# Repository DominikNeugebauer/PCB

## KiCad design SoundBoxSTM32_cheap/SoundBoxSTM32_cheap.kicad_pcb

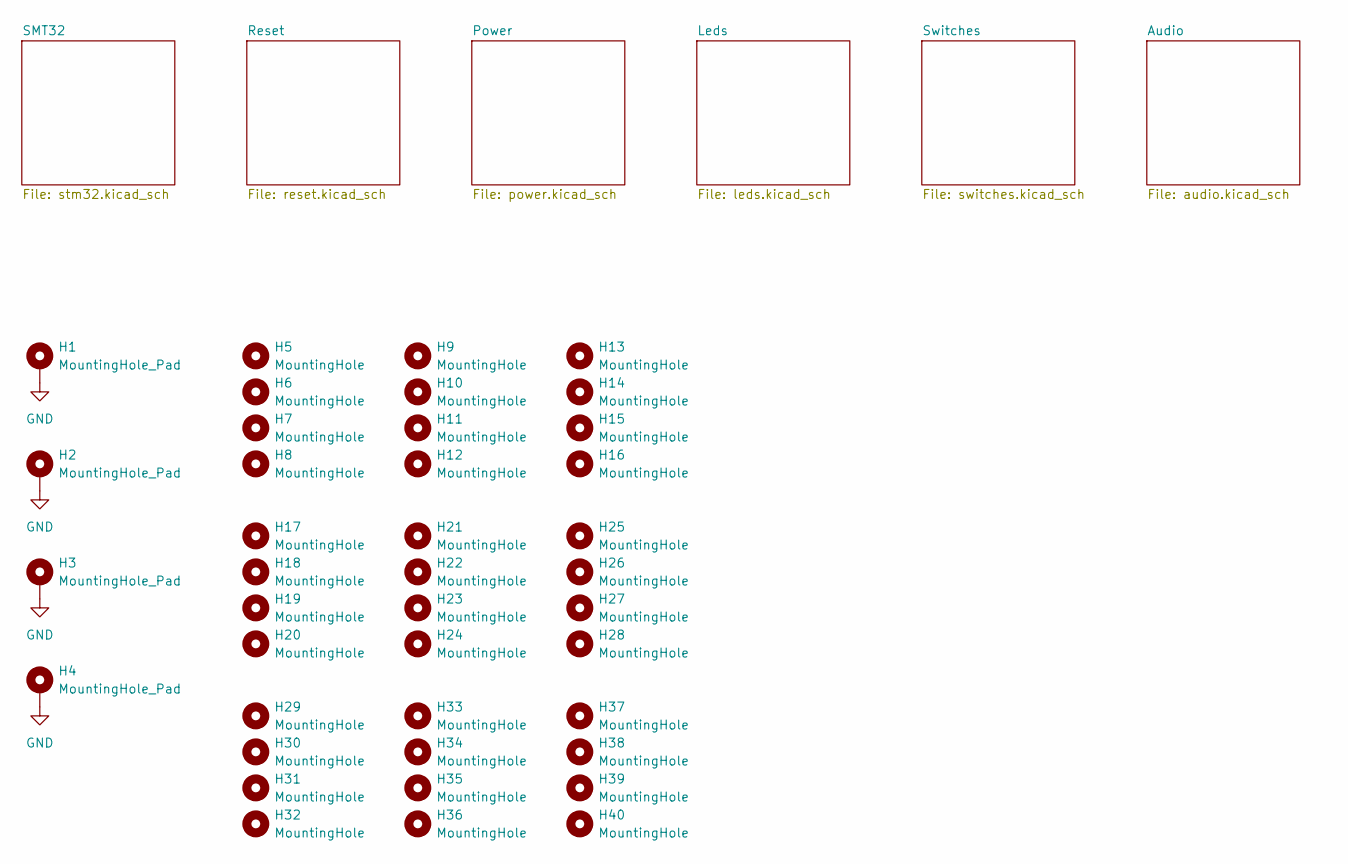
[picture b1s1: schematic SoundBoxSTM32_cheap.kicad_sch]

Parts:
H1, H2, H3, H4: MountingHole_Pad; MountingHole_5.3mm_M5_DIN965_Pad
H5, H6, H7, H8, H9, H10, H11, H12, H13, H14, H15, H16, H17, H18, H19, H20, H21, H22, H23, H24, H25, H26, H27, H28, H29, H30, H31, H32, H33, H34, H35, H36, H37, H38, H39, H40: MountingHole; MountingHole_5.3mm_M5

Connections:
GND: H1.1 (1_1), H2.1 (1_1), H3.1 (1_1), H4.1 (1_1); also elsewhere on the board

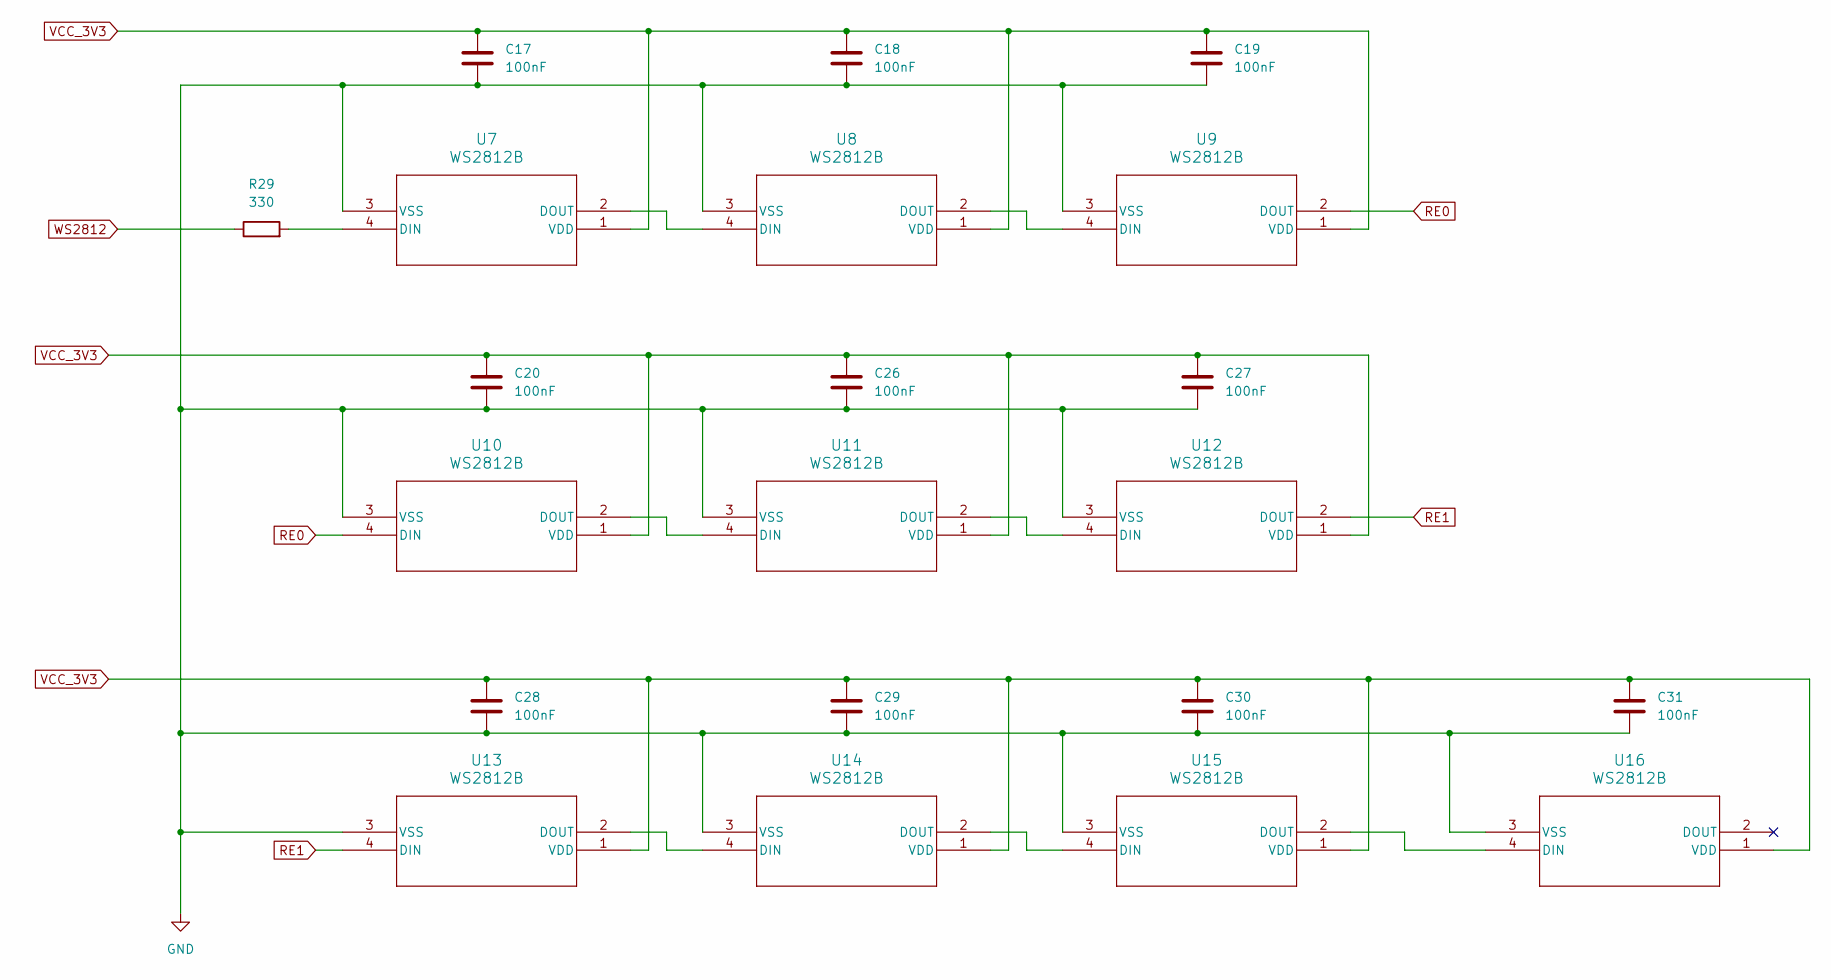
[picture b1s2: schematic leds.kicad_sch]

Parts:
C17, C18, C19, C20, C26, C27, C28, C29, C30, C31: 100nF; C_0603_1608Metric
R29: 330; R_0603_1608Metric
U7, U8, U9, U10, U11, U12, U13, U14, U15, U16: WS2812B; WS2812B_WDS

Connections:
GND: C17.2, C18.2, C19.2, C20.2, C26.2, C27.2, C28.2, C29.2, C30.2, C31.2, U7.3 (VSS), U8.3 (VSS), U9.3 (VSS), U10.3 (VSS), U11.3 (VSS), U12.3 (VSS), U13.3 (VSS), U14.3 (VSS), U15.3 (VSS), U16.3 (VSS); also elsewhere on the board
unnamed: R29.2, U7.4 (DIN)
unnamed: U7.2 (DOUT), U8.4 (DIN)
unnamed: U8.2 (DOUT), U9.4 (DIN)
unnamed: U10.2 (DOUT), U11.4 (DIN)
unnamed: U11.2 (DOUT), U12.4 (DIN)
unnamed: U13.2 (DOUT), U14.4 (DIN)
unnamed: U14.2 (DOUT), U15.4 (DIN)
unnamed: U15.2 (DOUT), U16.4 (DIN)
RE0: U9.2 (DOUT), U10.4 (DIN)
RE1: U12.2 (DOUT), U13.4 (DIN)
VCC_3V3: C17.1, C18.1, C19.1, C20.1, C26.1, C27.1, C28.1, C29.1, C30.1, C31.1, U7.1 (VDD), U8.1 (VDD), U9.1 (VDD), U10.1 (VDD), U11.1 (VDD), U12.1 (VDD), U13.1 (VDD), U14.1 (VDD), U15.1 (VDD), U16.1 (VDD); also elsewhere on the board
WS2812: R29.1; also elsewhere on the board

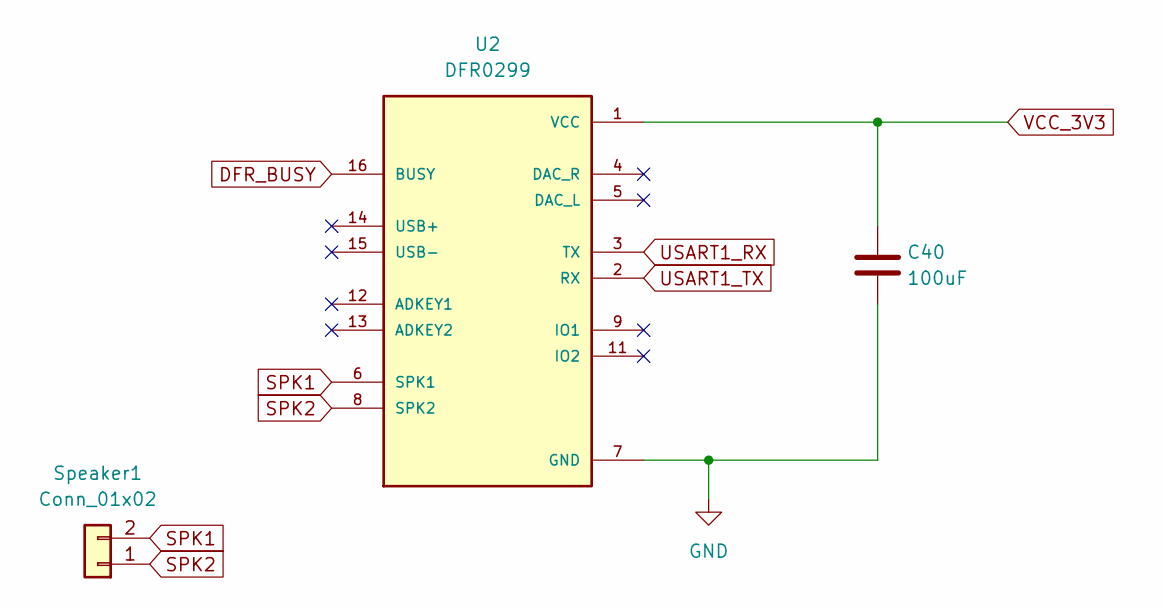
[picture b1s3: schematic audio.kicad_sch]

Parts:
C40: 100uF; C_1206_3216Metric_Pad1.33x1.80mm_HandSolder
Speaker1: Conn_01x02; PinHeader_1x02_P2.54mm_Vertical
U2: DFR0299

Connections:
DFR_BUSY: U2.16 (BUSY); also elsewhere on the board
GND: C40.2, U2.7 (GND), U2.10 (GND); also elsewhere on the board
SPK1: Speaker1.2, U2.6 (SPK1)
SPK2: Speaker1.1, U2.8 (SPK2)
USART1_RX: U2.3 (TX); also elsewhere on the board
USART1_TX: U2.2 (RX); also elsewhere on the board
VCC_3V3: C40.1, U2.1 (VCC); also elsewhere on the board

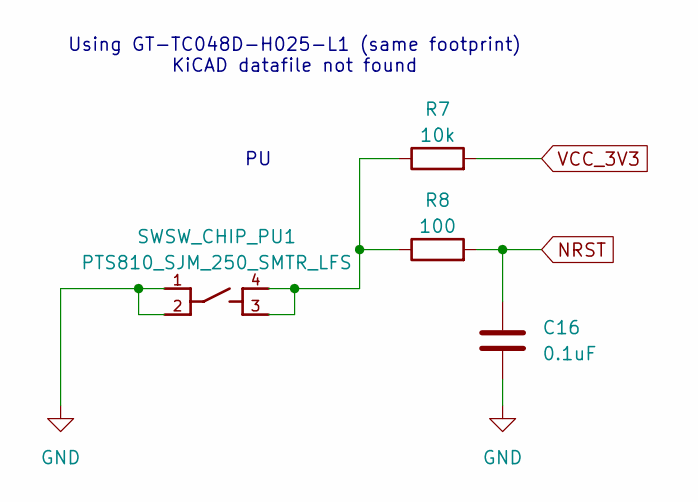
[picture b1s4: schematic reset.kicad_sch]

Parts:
C16: 0.1uF; C_0603_1608Metric
R7: 10k; R_0603_1608Metric
R8: 100; R_0603_1608Metric
SWSW_CHIP_PU1: PTS810_SJM_250_SMTR_LFS

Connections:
GND: C16.2, SWSW_CHIP_PU1.1, SWSW_CHIP_PU1.2; also elsewhere on the board
NRST: C16.1, R8.2; also elsewhere on the board
unnamed: R7.1, R8.1, SWSW_CHIP_PU1.3, SWSW_CHIP_PU1.4
VCC_3V3: R7.2; also elsewhere on the board

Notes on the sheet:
Using GT-TC048D-H025-L1 (same footprint) KiCAD datafile not found

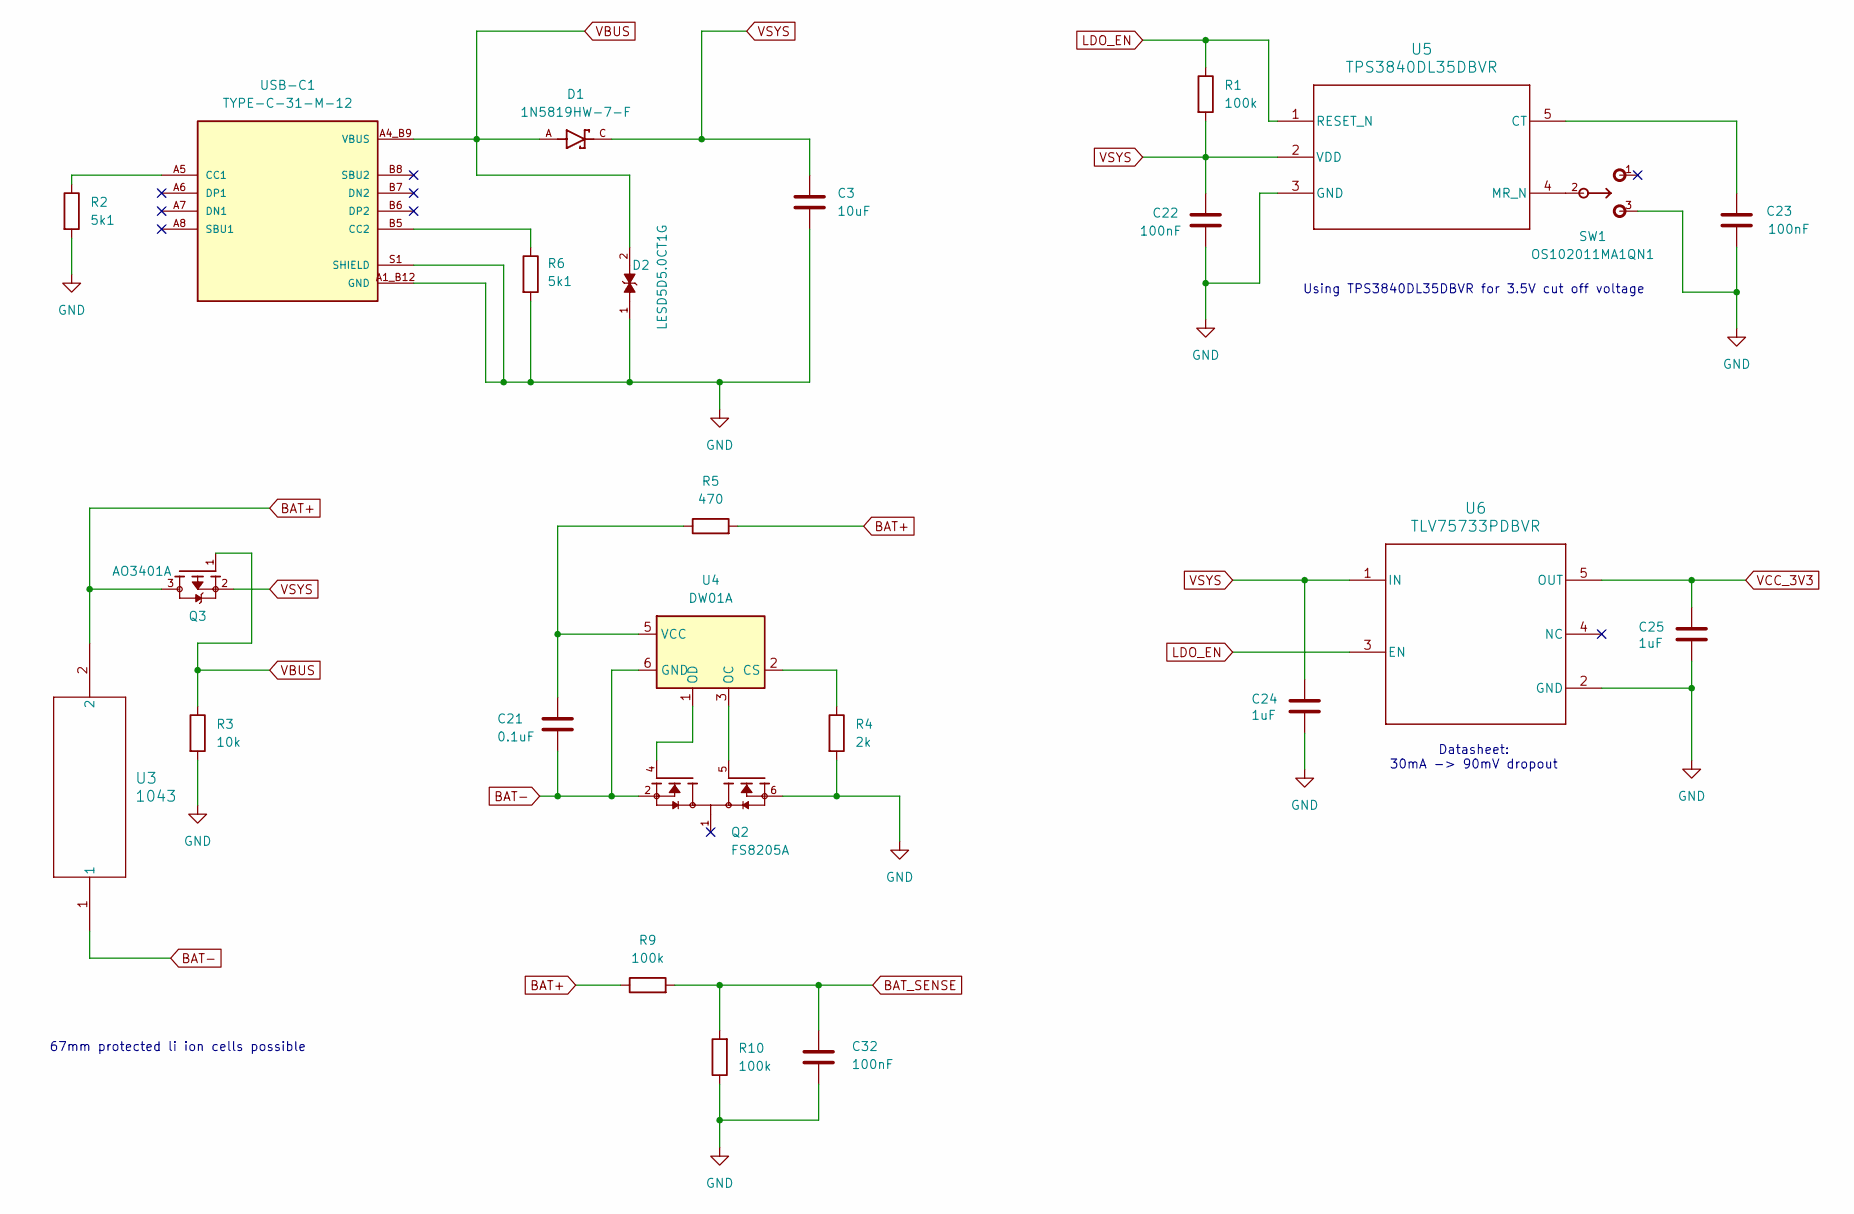
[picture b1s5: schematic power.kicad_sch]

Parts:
C3: 10uF; C_0603_1608Metric
C21: 0.1uF; C_0603_1608Metric
C22, C23, C32: 100nF; C_0603_1608Metric
C24, C25: 1uF; C_0603_1608Metric
D1: 1N5819HW-7-F; PARTREV 18-2
D2: LESD5D5.0CT1G; PARTREV O
Q2: FS8205A; PARTREV 1.7
Q3: AO3401A; PMOS-SOT23-3
R1, R9, R10: 100k; R_0603_1608Metric
R2, R6: 5k1; R_0603_1608Metric
R3: 10k; R_0603_1608Metric
R4: 2k; R_0603_1608Metric
R5: 470; R_0603_1608Metric
SW1: OS102011MA1QN1; MANUFACTURER_PART_NUMBER OS102011MA1QN1
U3: 1043; 1043_KEY
U4: DW01A; SOT-23-6
U5: TPS3840DL35DBVR; SOT-23-5
U6: TLV75733PDBVR; SOT95P280X145-5N_TLV75733PDBVR
USB-C1: TYPE-C-31-M-12; USB_TYPE-C-31-M-12; PARTREV 2020.12.08

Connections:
BAT+: Q3.3, R5.2, R9.1, U3.2
BAT-: C21.2, Q2.2, Q2.3, U3.1, U4.6 (GND)
BAT_SENSE: C32.1, R9.2, R10.2; also elsewhere on the board
GND: C3.2, C22.2, C23.2, C24.2, C25.2, C32.2, D2.1, Q2.6, Q2.7, R2.2, R3.2, R4.2, R6.2, R10.1, SW1.3, U5.3 (GND), U6.2 (GND), USB-C1.A1_B12 (GND), USB-C1.B1_A12 (GND), USB-C1.S1 (SHIELD), USB-C1.S2 (SHIELD), USB-C1.S3 (SHIELD), USB-C1.S4 (SHIELD); also elsewhere on the board
LDO_EN: R1.1, U5.1 (RESET_N), U6.3 (EN)
unnamed: R4.1, U4.2 (CS)
unnamed: Q2.5, U4.3 (OC)
unnamed: Q2.4, U4.1 (OD)
unnamed: C21.1, R5.1, U4.5 (VCC)
unnamed: C23.1, U5.5 (CT)
unnamed: SW1.2, U5.4 (MR_N)
unnamed: R2.1, USB-C1.A5 (CC1)
unnamed: R6.1, USB-C1.B5 (CC2)
VBUS: D1.A, D2.2, Q3.1, R3.1, USB-C1.A4_B9 (VBUS), USB-C1.B4_A9 (VBUS)
VCC_3V3: C25.1, U6.5 (OUT); also elsewhere on the board
VSYS: C3.1, C22.1, C24.1, D1.C, Q3.2, R1.2, U5.2 (VDD), U6.1 (IN)

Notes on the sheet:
Using TPS3840DL35DBVR for 3.5V cut off voltage
67mm protected li ion cells possible
Datasheet: 30mA -> 90mV dropout

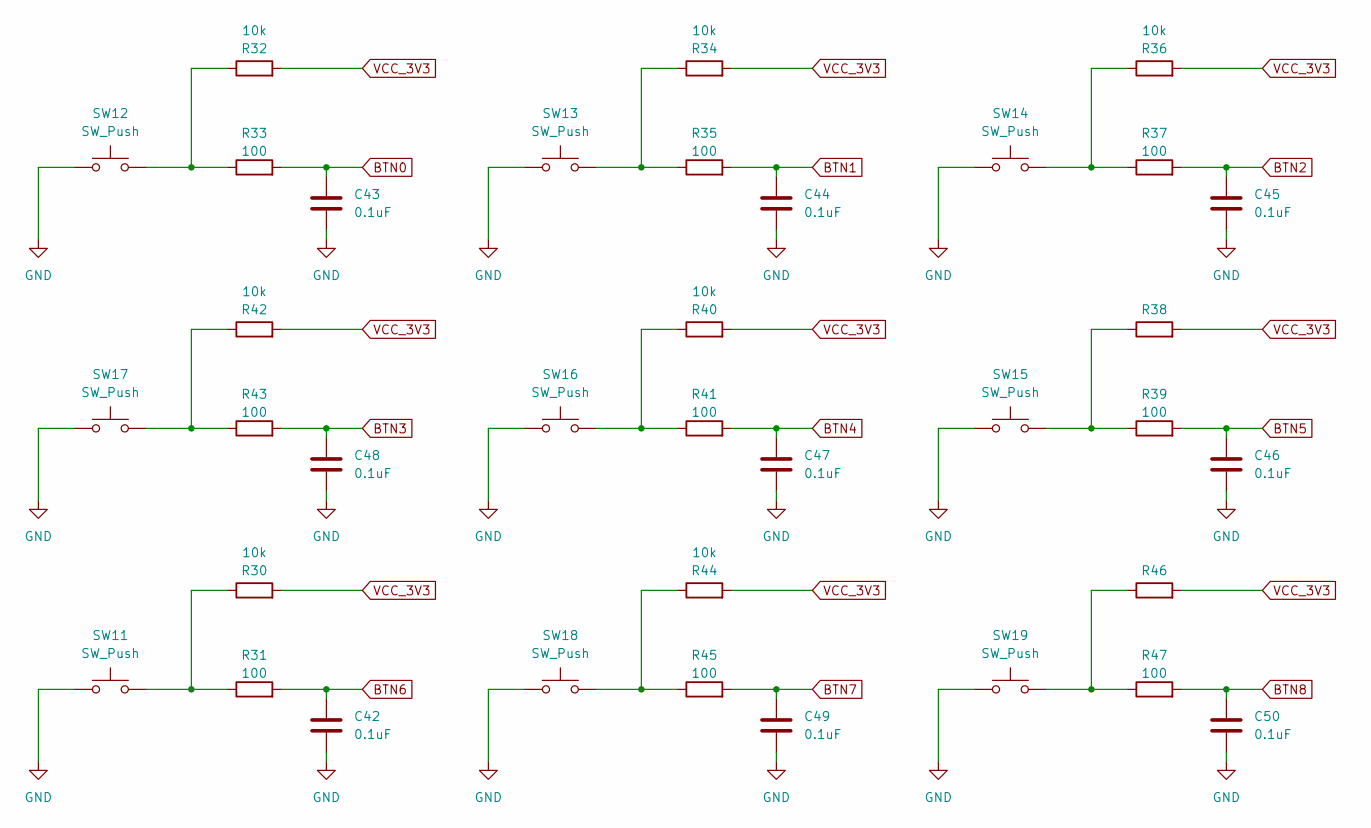
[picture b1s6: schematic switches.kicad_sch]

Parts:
C42, C43, C44, C45, C46, C47, C48, C49, C50: 0.1uF; C_0603_1608Metric
R30, R32, R34, R36, R38, R40, R42, R44, R46: 10k; R_0603_1608Metric
R31, R33, R35, R37, R39, R41, R43, R45, R47: 100; R_0603_1608Metric
SW11, SW12, SW13, SW14, SW15, SW16, SW17, SW18, SW19: SW_Push; SW_Cherry_MX_1.00u_PCB

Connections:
BTN0: C43.1, R33.2; also elsewhere on the board
BTN1: C44.1, R35.2; also elsewhere on the board
BTN2: C45.1, R37.2; also elsewhere on the board
BTN3: C48.1, R43.2; also elsewhere on the board
BTN4: C47.1, R41.2; also elsewhere on the board
BTN5: C46.1, R39.2; also elsewhere on the board
BTN6: C42.1, R31.2; also elsewhere on the board
BTN7: C49.1, R45.2; also elsewhere on the board
BTN8: C50.1, R47.2; also elsewhere on the board
GND: C42.2, C43.2, C44.2, C45.2, C46.2, C47.2, C48.2, C49.2, C50.2, SW11.1, SW12.1, SW13.1, SW14.1, SW15.1, SW16.1, SW17.1, SW18.1, SW19.1; also elsewhere on the board
unnamed: R30.1, R31.1, SW11.2
unnamed: R32.1, R33.1, SW12.2
unnamed: R34.1, R35.1, SW13.2
unnamed: R36.1, R37.1, SW14.2
unnamed: R38.1, R39.1, SW15.2
unnamed: R40.1, R41.1, SW16.2
unnamed: R42.1, R43.1, SW17.2
unnamed: R44.1, R45.1, SW18.2
unnamed: R46.1, R47.1, SW19.2
VCC_3V3: R30.2, R32.2, R34.2, R36.2, R38.2, R40.2, R42.2, R44.2, R46.2; also elsewhere on the board

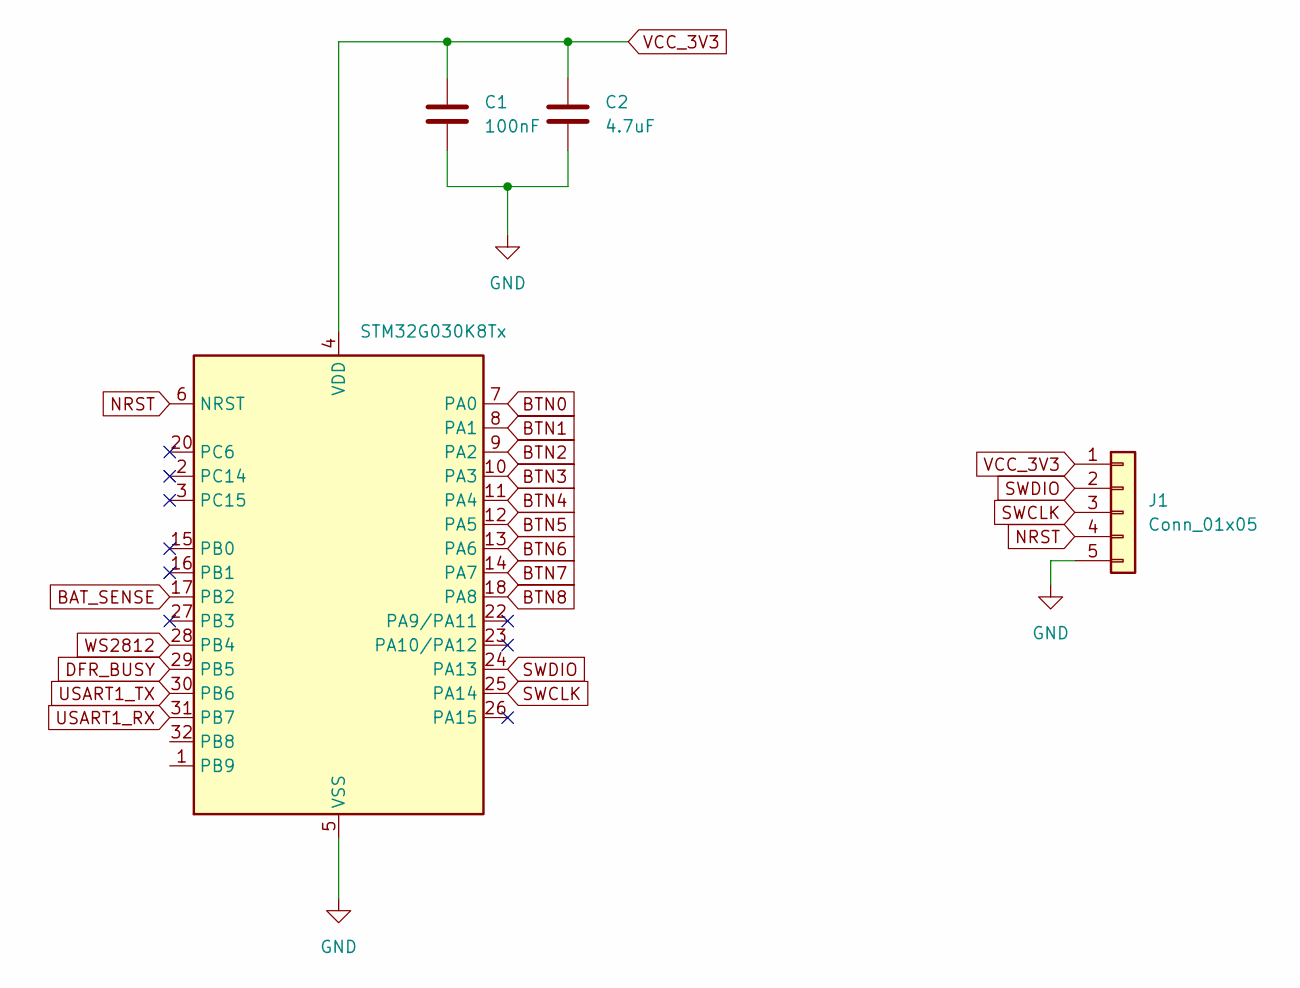
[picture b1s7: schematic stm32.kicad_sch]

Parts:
C1: 100nF; C_0603_1608Metric
C2: 4.7uF; C_0603_1608Metric
J1: Conn_01x05; PinHeader_1x05_P2.54mm_Vertical
U1: STM32G030K8Tx; LQFP-32_7x7mm_P0.8mm

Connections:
BAT_SENSE: U1.17 (PB2); also elsewhere on the board
BTN0: U1.7 (PA0); also elsewhere on the board
BTN1: U1.8 (PA1); also elsewhere on the board
BTN2: U1.9 (PA2); also elsewhere on the board
BTN3: U1.10 (PA3); also elsewhere on the board
BTN4: U1.11 (PA4); also elsewhere on the board
BTN5: U1.12 (PA5); also elsewhere on the board
BTN6: U1.13 (PA6); also elsewhere on the board
BTN7: U1.14 (PA7); also elsewhere on the board
BTN8: U1.18 (PA8); also elsewhere on the board
DFR_BUSY: U1.29 (PB5); also elsewhere on the board
GND: C1.2, C2.2, J1.5, U1.5 (VSS); also elsewhere on the board
NRST: J1.4, U1.6 (NRST); also elsewhere on the board
SWCLK: J1.3, U1.25 (PA14)
SWDIO: J1.2, U1.24 (PA13)
USART1_RX: U1.31 (PB7); also elsewhere on the board
USART1_TX: U1.30 (PB6); also elsewhere on the board
VCC_3V3: C1.1, C2.1, J1.1, U1.4 (VDD); also elsewhere on the board
WS2812: U1.28 (PB4); also elsewhere on the board

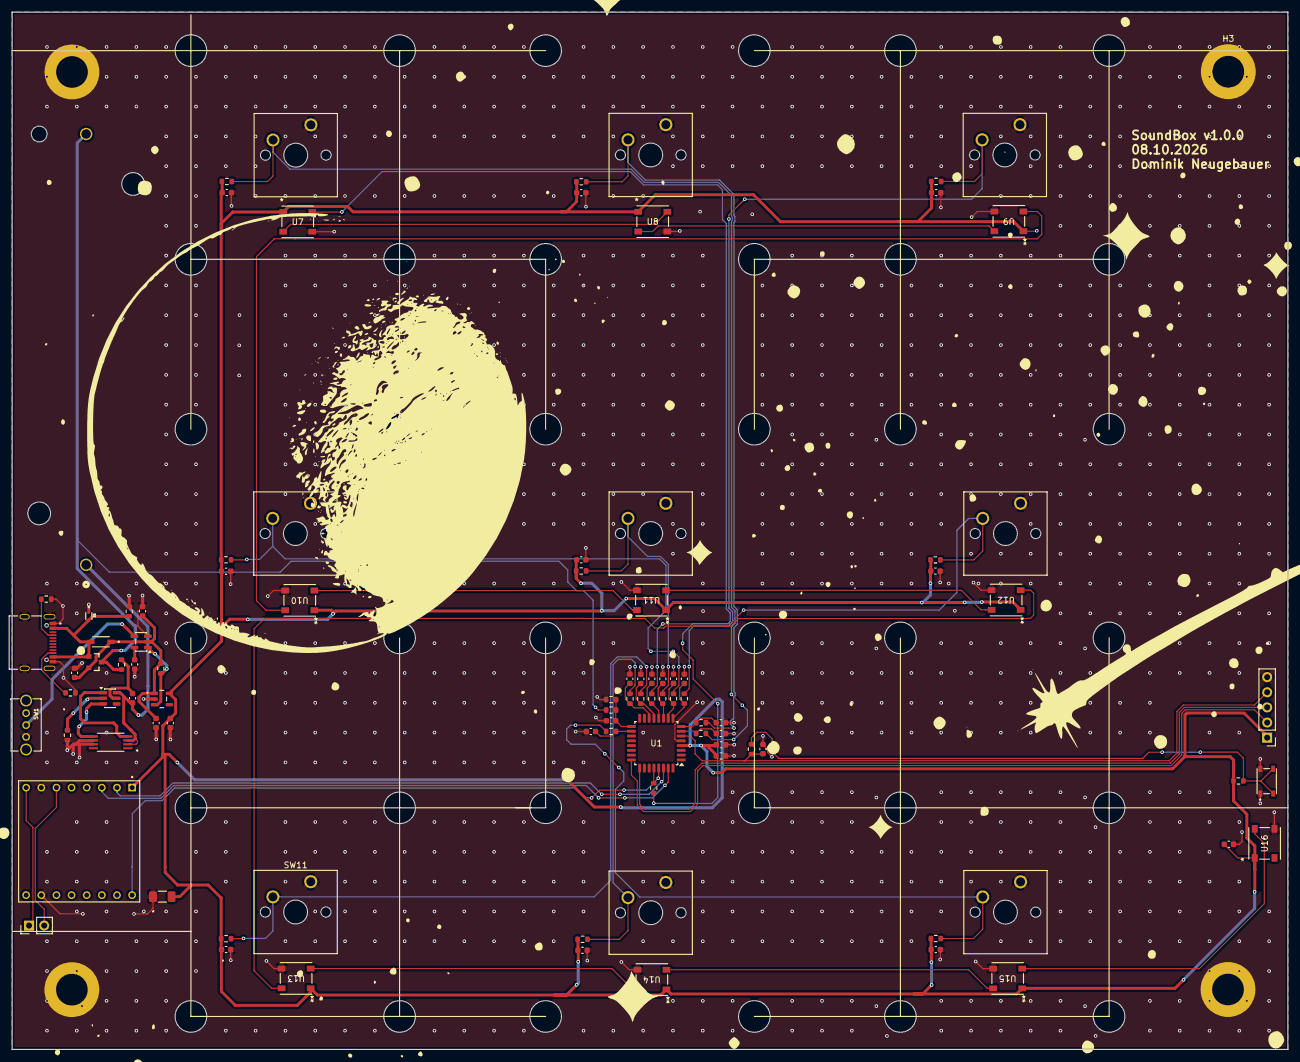
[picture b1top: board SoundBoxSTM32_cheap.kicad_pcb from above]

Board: 2 copper layers, 214.0 x 174.0 mm, 133 parts (1 on the bottom side), 54 nets.

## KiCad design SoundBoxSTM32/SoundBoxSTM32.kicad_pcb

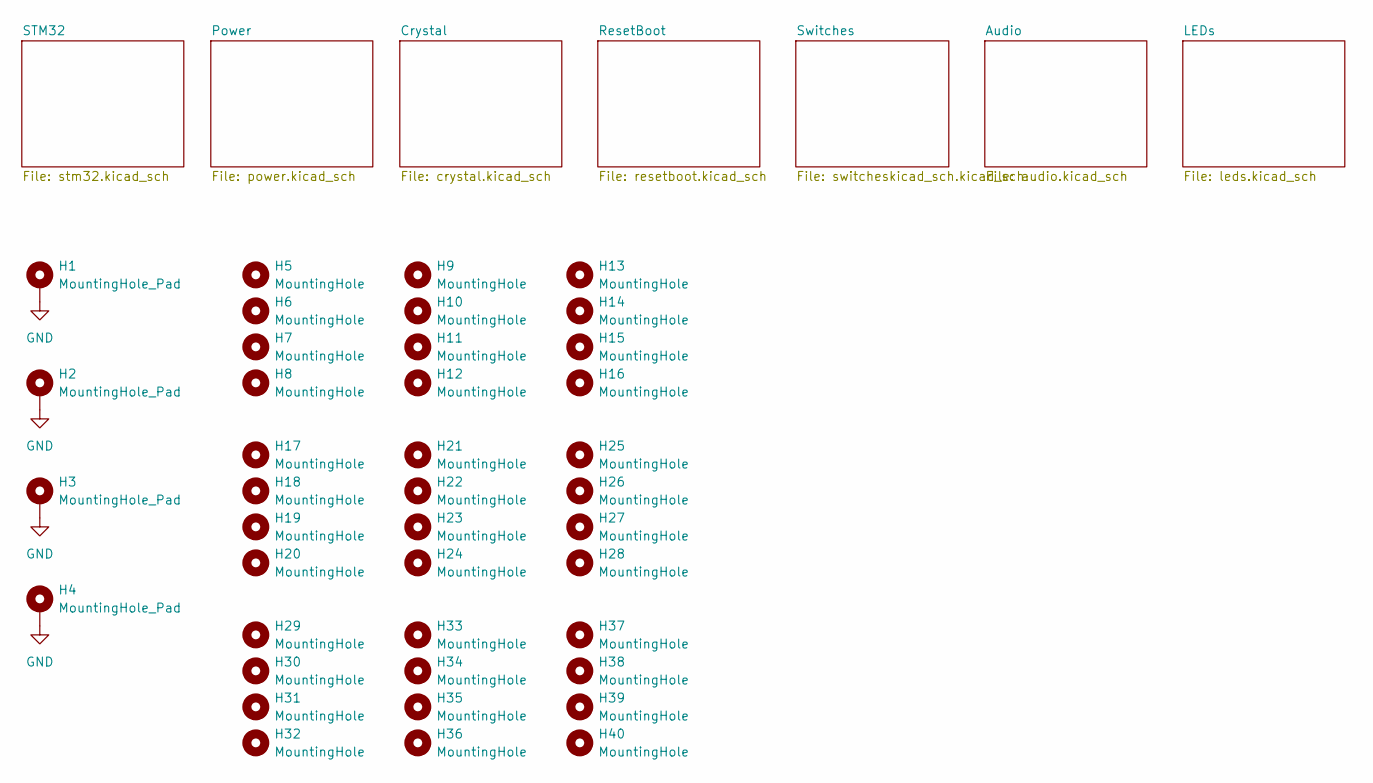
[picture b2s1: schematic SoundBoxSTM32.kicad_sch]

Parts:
H1, H2, H3, H4: MountingHole_Pad; MountingHole_5.3mm_M5_DIN965_Pad
H5, H6, H7, H8, H9, H10, H11, H12, H13, H14, H15, H16, H17, H18, H19, H20, H21, H22, H23, H24, H25, H26, H27, H28, H29, H30, H31, H32, H33, H34, H35, H36, H37, H38, H39, H40: MountingHole; MountingHole_5.3mm_M5

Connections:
GND: H1.1 (1_1), H2.1 (1_1), H3.1 (1_1), H4.1 (1_1); also elsewhere on the board

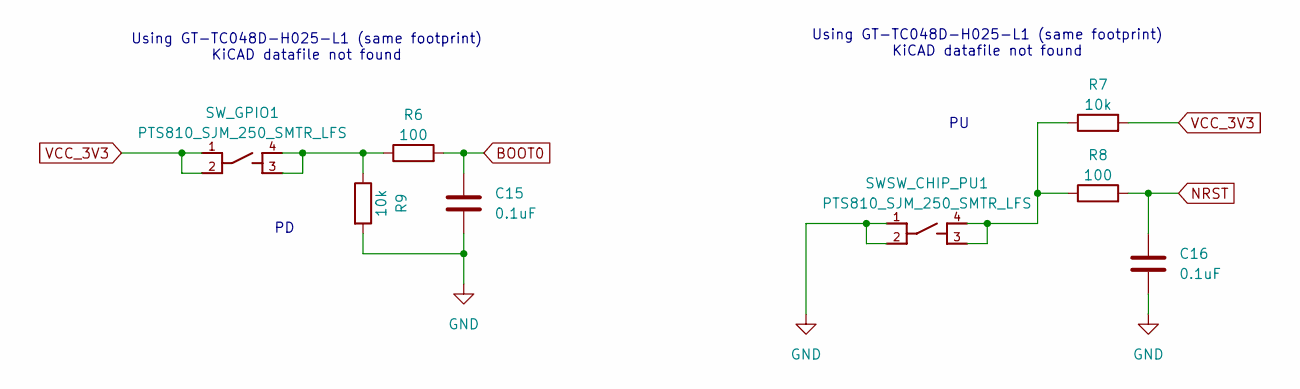
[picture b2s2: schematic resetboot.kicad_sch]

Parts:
C15, C16: 0.1uF; C_0603_1608Metric
R6, R8: 100; R_0603_1608Metric
R7, R9: 10k; R_0603_1608Metric
SWSW_CHIP_PU1: PTS810_SJM_250_SMTR_LFS
SW_GPIO1: PTS810_SJM_250_SMTR_LFS

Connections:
BOOT0: C15.1, R6.2; also elsewhere on the board
GND: C15.2, C16.2, R9.2, SWSW_CHIP_PU1.1, SWSW_CHIP_PU1.2; also elsewhere on the board
NRST: C16.1, R8.2; also elsewhere on the board
unnamed: R6.1, R9.1, SW_GPIO1.3, SW_GPIO1.4
unnamed: R7.1, R8.1, SWSW_CHIP_PU1.3, SWSW_CHIP_PU1.4
VCC_3V3: R7.2, SW_GPIO1.1, SW_GPIO1.2; also elsewhere on the board

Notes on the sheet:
Using GT-TC048D-H025-L1 (same footprint) KiCAD datafile not found

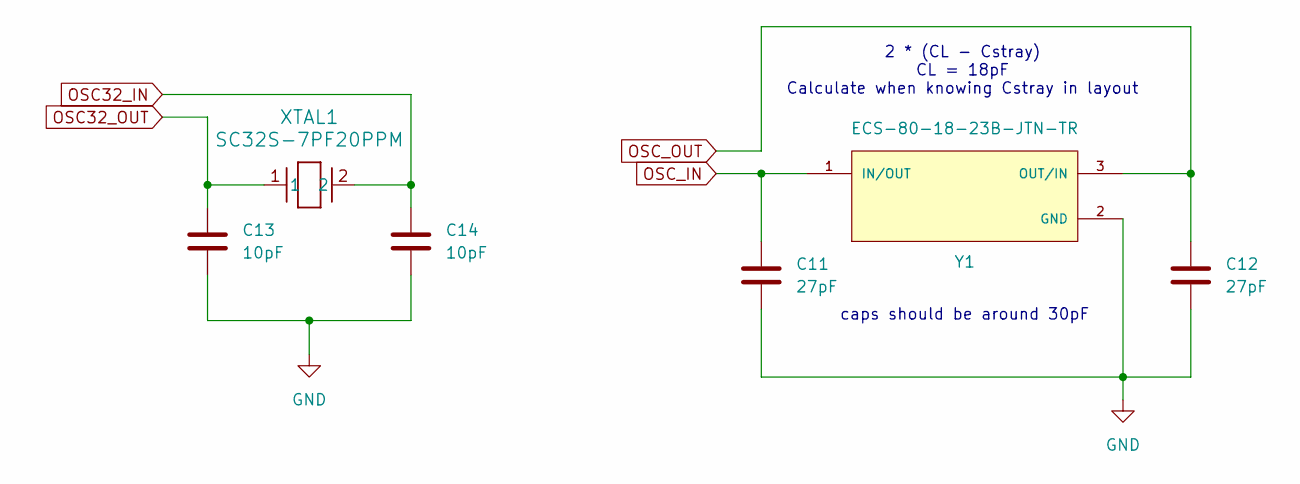
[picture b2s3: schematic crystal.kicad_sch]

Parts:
C11, C12: 27pF; C_0603_1608Metric
C13, C14: 10pF; C_0603_1608Metric
XTAL1: SC32S-7PF20PPM; XTAL_SC32S-7PF20PPM_EPS
Y1: ECS-80-18-23B-JTN-TR; XTAL_ECS-80-18-23B-JTN-TR

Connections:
GND: C11.2, C12.2, C13.2, C14.2, Y1.2 (GND), Y1.4 (GND); also elsewhere on the board
OSC32_IN: C14.1, XTAL1.2; also elsewhere on the board
OSC32_OUT: C13.1, XTAL1.1; also elsewhere on the board
OSC_IN: C11.1, Y1.1 (IN/OUT); also elsewhere on the board
OSC_OUT: C12.1, Y1.3 (OUT/IN); also elsewhere on the board

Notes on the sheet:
2 * (CL - Cstray) CL = 18pF Calculate when knowing Cstray in layout
caps should be around 30pF

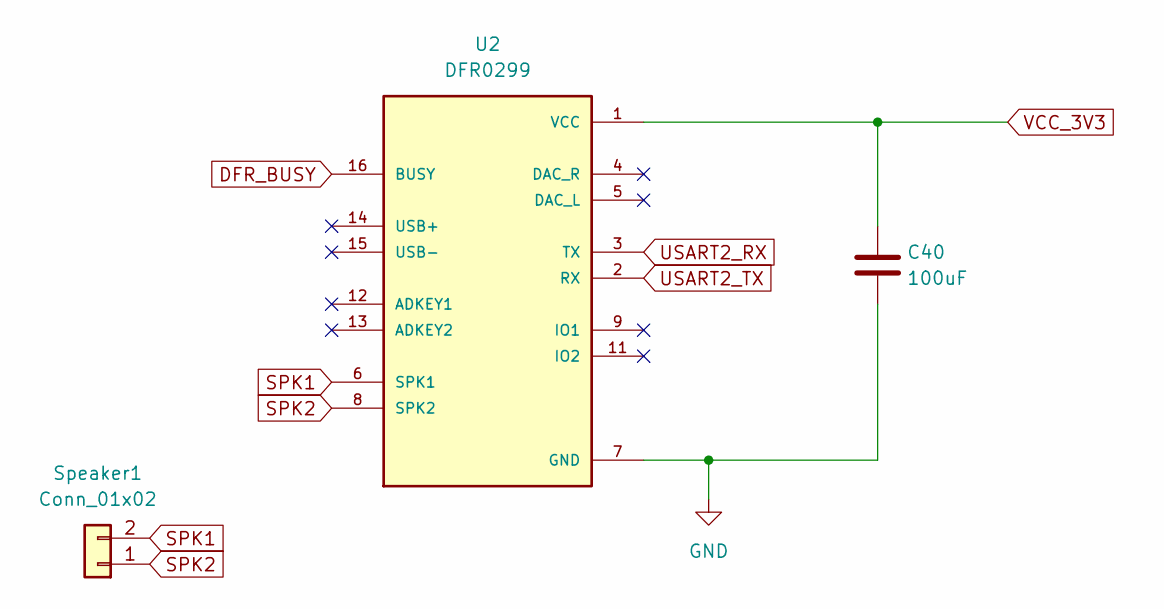
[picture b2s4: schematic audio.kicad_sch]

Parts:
C40: 100uF; C_0603_1608Metric
Speaker1: Conn_01x02; PinHeader_1x02_P2.54mm_Vertical
U2: DFR0299

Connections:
DFR_BUSY: U2.16 (BUSY); also elsewhere on the board
GND: C40.2, U2.7 (GND), U2.10 (GND); also elsewhere on the board
SPK1: Speaker1.2, U2.6 (SPK1)
SPK2: Speaker1.1, U2.8 (SPK2)
USART2_RX: U2.3 (TX); also elsewhere on the board
USART2_TX: U2.2 (RX); also elsewhere on the board
VCC_3V3: C40.1, U2.1 (VCC); also elsewhere on the board

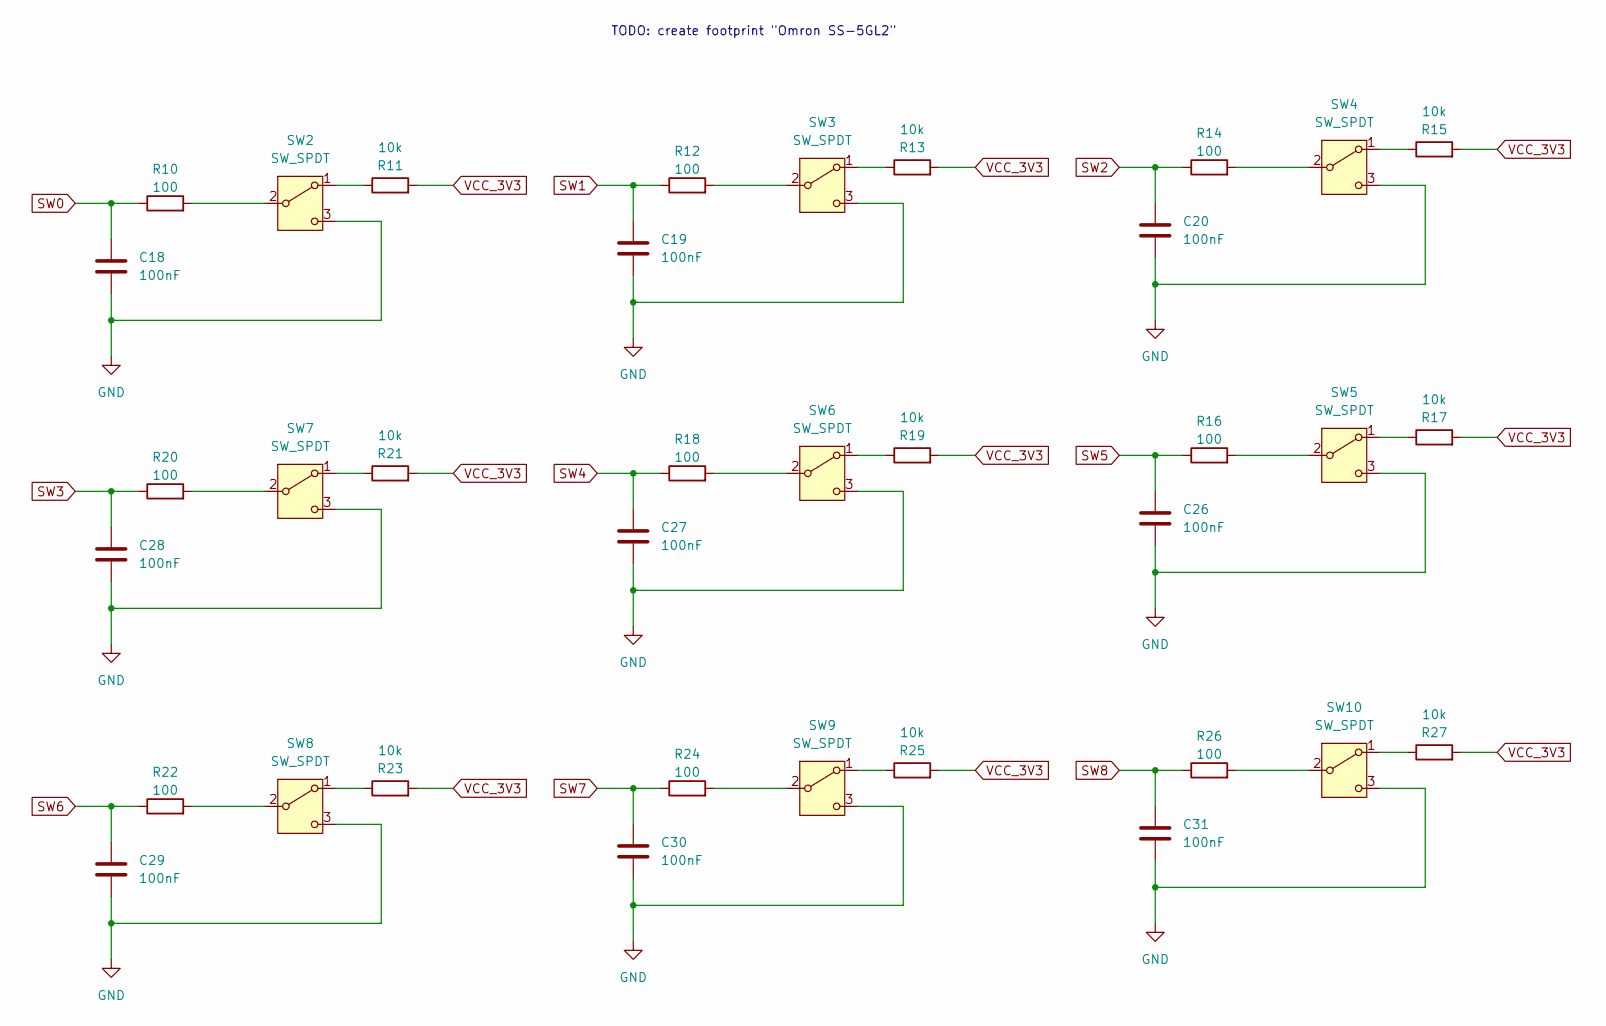
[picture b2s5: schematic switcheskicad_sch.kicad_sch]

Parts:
C18, C19, C20, C26, C27, C28, C29, C30, C31: 100nF; C_0603_1608Metric
R10, R12, R14, R16, R18, R20, R22, R24, R26: 100; R_0603_1608Metric
R11, R13, R15, R17, R19, R21, R23, R25, R27: 10k; R_0603_1608Metric
SW2, SW3, SW4, SW5, SW6, SW7, SW8, SW9, SW10: SW_SPDT; D2F-01L_OMR

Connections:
GND: C18.2, C19.2, C20.2, C26.2, C27.2, C28.2, C29.2, C30.2, C31.2, SW2.3 (C), SW3.3 (C), SW4.3 (C), SW5.3 (C), SW6.3 (C), SW7.3 (C), SW8.3 (C), SW9.3 (C), SW10.3 (C); also elsewhere on the board
unnamed: R11.1, SW2.1 (A)
unnamed: R10.2, SW2.2 (B)
unnamed: R13.1, SW3.1 (A)
unnamed: R12.2, SW3.2 (B)
unnamed: R15.1, SW4.1 (A)
unnamed: R14.2, SW4.2 (B)
unnamed: R17.1, SW5.1 (A)
unnamed: R16.2, SW5.2 (B)
unnamed: R19.1, SW6.1 (A)
unnamed: R18.2, SW6.2 (B)
unnamed: R21.1, SW7.1 (A)
unnamed: R20.2, SW7.2 (B)
unnamed: R23.1, SW8.1 (A)
unnamed: R22.2, SW8.2 (B)
unnamed: R25.1, SW9.1 (A)
unnamed: R24.2, SW9.2 (B)
unnamed: R27.1, SW10.1 (A)
unnamed: R26.2, SW10.2 (B)
SW0: C18.1, R10.1; also elsewhere on the board
SW1: C19.1, R12.1; also elsewhere on the board
SW2: C20.1, R14.1; also elsewhere on the board
SW3: C28.1, R20.1; also elsewhere on the board
SW4: C27.1, R18.1; also elsewhere on the board
SW5: C26.1, R16.1; also elsewhere on the board
SW6: C29.1, R22.1; also elsewhere on the board
SW7: C30.1, R24.1; also elsewhere on the board
SW8: C31.1, R26.1; also elsewhere on the board
VCC_3V3: R11.2, R13.2, R15.2, R17.2, R19.2, R21.2, R23.2, R25.2, R27.2; also elsewhere on the board

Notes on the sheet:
TODO: create footprint "Omron SS-5GL2"

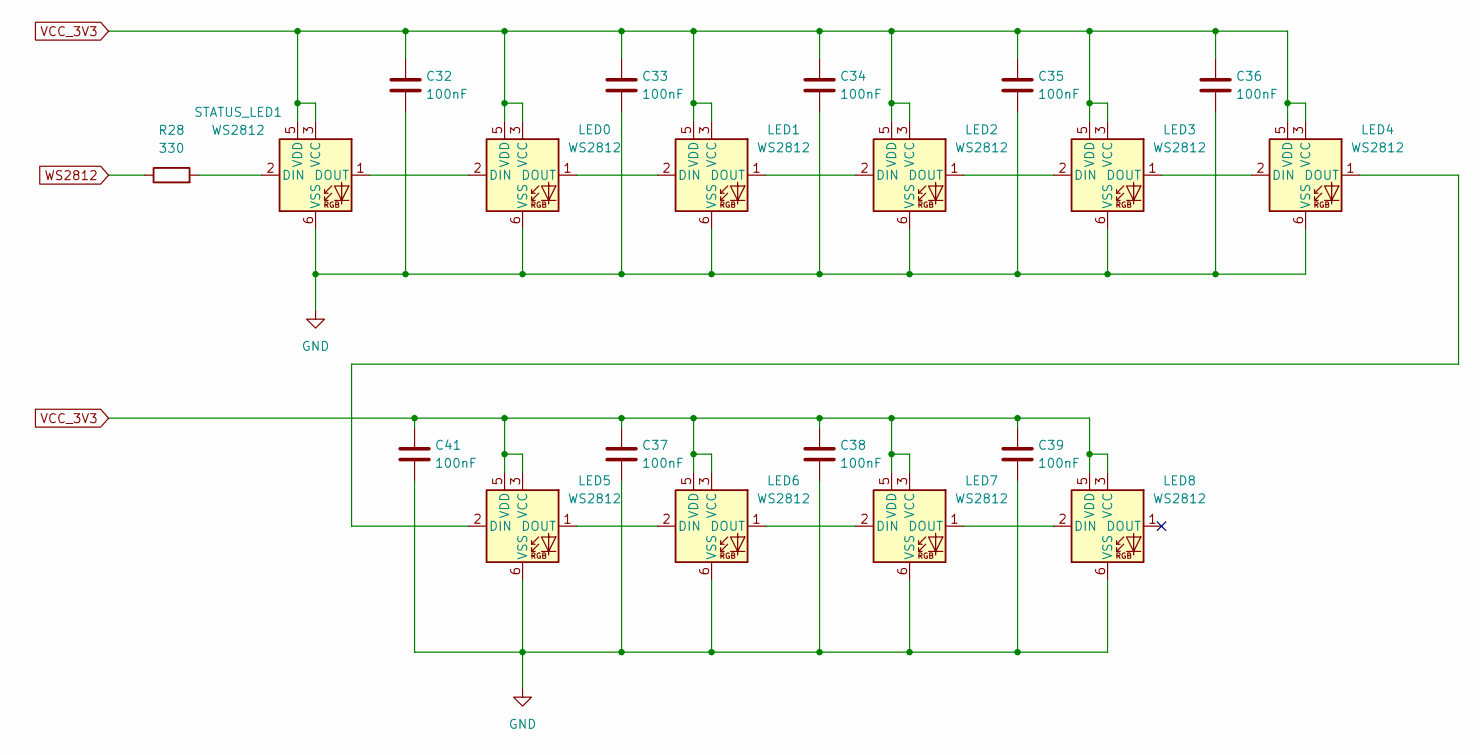
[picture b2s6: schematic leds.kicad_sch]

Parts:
C32, C33, C34, C35, C36, C37, C38, C39, C41: 100nF; C_0603_1608Metric
LED0, LED1, LED2, LED3, LED4, LED5, LED6, LED7, LED8: WS2812; LED_WS2812_PLCC6_5.0x5.0mm_P1.6mm
R28: 330; R_0603_1608Metric
STATUS_LED1: WS2812; LED_WS2812_PLCC6_5.0x5.0mm_P1.6mm

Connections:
GND: C32.2, C33.2, C34.2, C35.2, C36.2, C37.2, C38.2, C39.2, C41.2, LED0.6 (VSS), LED1.6 (VSS), LED2.6 (VSS), LED3.6 (VSS), LED4.6 (VSS), LED5.6 (VSS), LED6.6 (VSS), LED7.6 (VSS), LED8.6 (VSS), STATUS_LED1.6 (VSS); also elsewhere on the board
unnamed: LED0.2 (DIN), STATUS_LED1.1 (DOUT)
unnamed: LED0.1 (DOUT), LED1.2 (DIN)
unnamed: LED1.1 (DOUT), LED2.2 (DIN)
unnamed: LED2.1 (DOUT), LED3.2 (DIN)
unnamed: LED3.1 (DOUT), LED4.2 (DIN)
unnamed: LED4.1 (DOUT), LED5.2 (DIN)
unnamed: LED5.1 (DOUT), LED6.2 (DIN)
unnamed: LED6.1 (DOUT), LED7.2 (DIN)
unnamed: LED7.1 (DOUT), LED8.2 (DIN)
unnamed: R28.2, STATUS_LED1.2 (DIN)
VCC_3V3: C32.1, C33.1, C34.1, C35.1, C36.1, C37.1, C38.1, C39.1, C41.1, LED0.3 (VCC), LED0.5 (VDD), LED1.3 (VCC), LED1.5 (VDD), LED2.3 (VCC), LED2.5 (VDD), LED3.3 (VCC), LED3.5 (VDD), LED4.3 (VCC), LED4.5 (VDD), LED5.3 (VCC), LED5.5 (VDD), LED6.3 (VCC), LED6.5 (VDD), LED7.3 (VCC), LED7.5 (VDD), LED8.3 (VCC), LED8.5 (VDD), STATUS_LED1.3 (VCC), STATUS_LED1.5 (VDD); also elsewhere on the board
WS2812: R28.1; also elsewhere on the board

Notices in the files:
parts and their libraries:
COPYRIGHT: Copyright (C) 2024 Ultra Librarian. All rights reserved.
